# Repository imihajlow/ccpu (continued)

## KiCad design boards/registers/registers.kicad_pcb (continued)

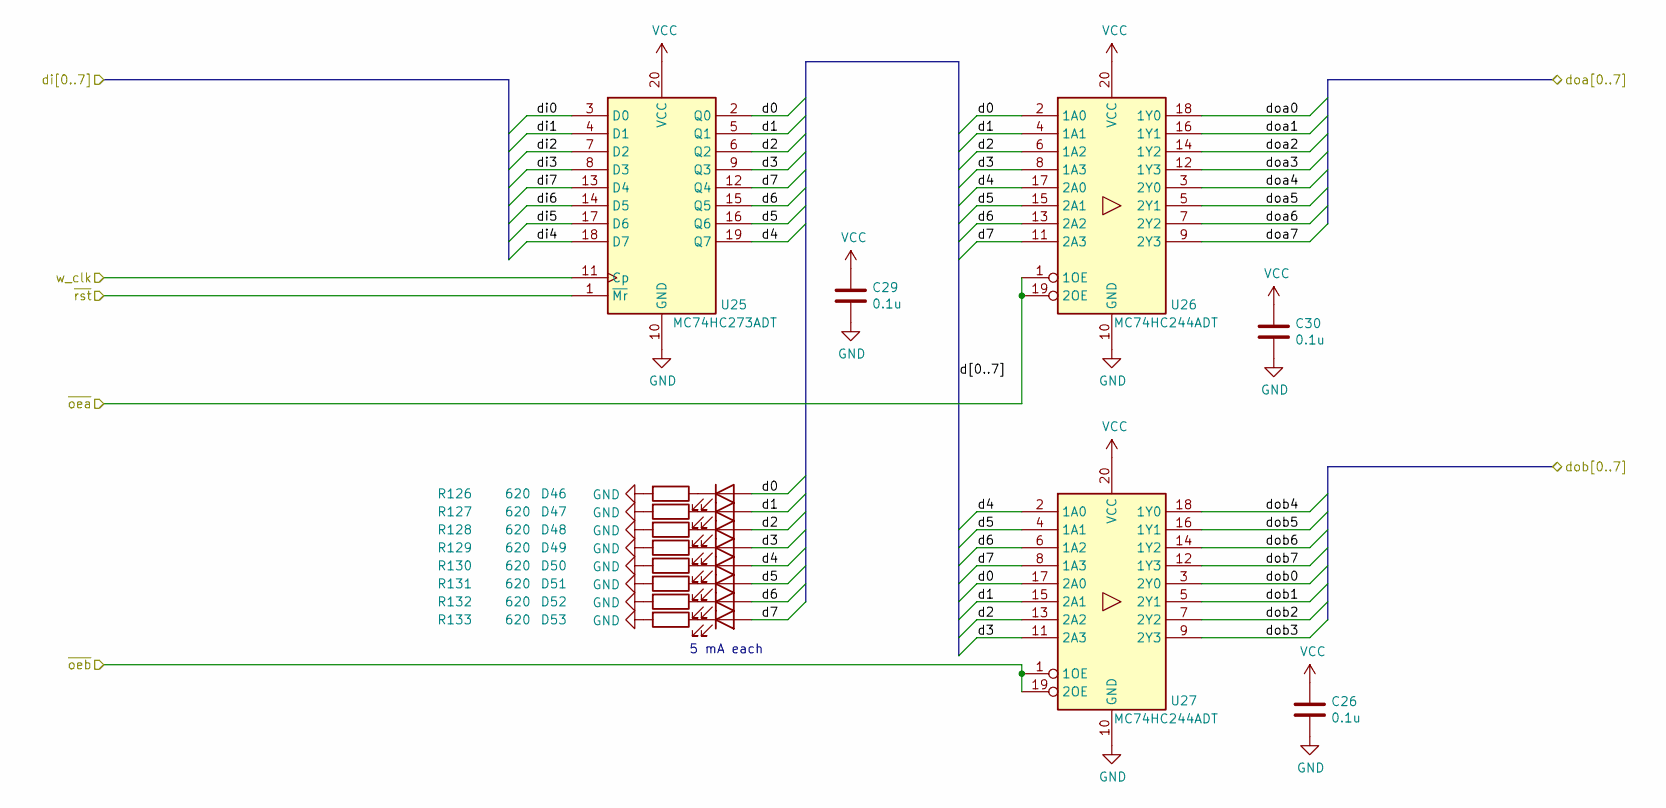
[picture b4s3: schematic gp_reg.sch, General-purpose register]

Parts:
C26, C29, C30: 0.1u; C_0805_2012Metric
D46, D47, D48, D49, D50, D51, D52, D53: KP-2012EC; LED_0805_2012Metric
R126, R127, R128, R129, R130, R131, R132, R133: 620; R_0805_2012Metric
U25: MC74HC273ADT; TSSOP-20_4.4x6.5mm_P0.65mm
U26, U27: MC74HC244ADT; TSSOP-20_4.4x6.5mm_P0.65mm

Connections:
/alu_b0: U27.3 (2Y0); also elsewhere on the board
/alu_b1: U27.5 (2Y1); also elsewhere on the board
/alu_b2: U27.7 (2Y2); also elsewhere on the board
/alu_b3: U27.9 (2Y3); also elsewhere on the board
/alu_b4: U27.18 (1Y0); also elsewhere on the board
/alu_b5: U27.16 (1Y1); also elsewhere on the board
/alu_b6: U27.14 (1Y2); also elsewhere on the board
/alu_b7: U27.12 (1Y3); also elsewhere on the board
/b_w_clk: U25.11 (Cp); also elsewhere on the board
/d0: U26.18 (1Y0); also elsewhere on the board
/d1: U26.16 (1Y1); also elsewhere on the board
/d2: U26.14 (1Y2); also elsewhere on the board
/d3: U26.12 (1Y3); also elsewhere on the board
/d4: U26.3 (2Y0); also elsewhere on the board
/d5: U26.5 (2Y1); also elsewhere on the board
/d6: U26.7 (2Y2); also elsewhere on the board
/d7: U26.9 (2Y3); also elsewhere on the board
/di0: U25.3 (D0); also elsewhere on the board
/di1: U25.4 (D1); also elsewhere on the board
/di2: U25.7 (D2); also elsewhere on the board
/di3: U25.8 (D3); also elsewhere on the board
/di4: U25.18 (D7); also elsewhere on the board
/di5: U25.17 (D6); also elsewhere on the board
/di6: U25.14 (D5); also elsewhere on the board
/di7: U25.13 (D4); also elsewhere on the board
/gp_reg_b/d0: D46.2 (A), U25.2 (Q0), U26.2 (1A0), U27.17 (2A0)
/gp_reg_b/d1: D47.2 (A), U25.5 (Q1), U26.4 (1A1), U27.15 (2A1)
/gp_reg_b/d2: D48.2 (A), U25.6 (Q2), U26.6 (1A2), U27.13 (2A2)
/gp_reg_b/d3: D49.2 (A), U25.9 (Q3), U26.8 (1A3), U27.11 (2A3)
/gp_reg_b/d4: D50.2 (A), U25.19 (Q7), U26.17 (2A0), U27.2 (1A0)
/gp_reg_b/d5: D51.2 (A), U25.16 (Q6), U26.15 (2A1), U27.4 (1A1)
/gp_reg_b/d6: D52.2 (A), U25.15 (Q5), U26.13 (2A2), U27.6 (1A2)
/gp_reg_b/d7: D53.2 (A), U25.12 (Q4), U26.11 (2A3), U27.8 (1A3)
/~oe_b_alu: U27.1 (1OE), U27.19 (2OE); also elsewhere on the board
/~oe_b_d: U26.1 (1OE), U26.19 (2OE); also elsewhere on the board
/~rst: U25.1 (~Mr); also elsewhere on the board
GND: C26.2, C29.2, C30.2, R126.2, R127.2, R128.2, R129.2, R130.2, R131.2, R132.2, R133.2, U25.10 (GND), U26.10 (GND), U27.10 (GND); also elsewhere on the board
unnamed: D46.1 (K), R126.1
unnamed: D47.1 (K), R127.1
unnamed: D48.1 (K), R128.1
unnamed: D49.1 (K), R129.1
unnamed: D50.1 (K), R130.1
unnamed: D51.1 (K), R131.1
unnamed: D52.1 (K), R132.1
unnamed: D53.1 (K), R133.1
VCC: C26.1, C29.1, C30.1, U25.20 (VCC), U26.20 (VCC), U27.20 (VCC); also elsewhere on the board

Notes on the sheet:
5 mA each

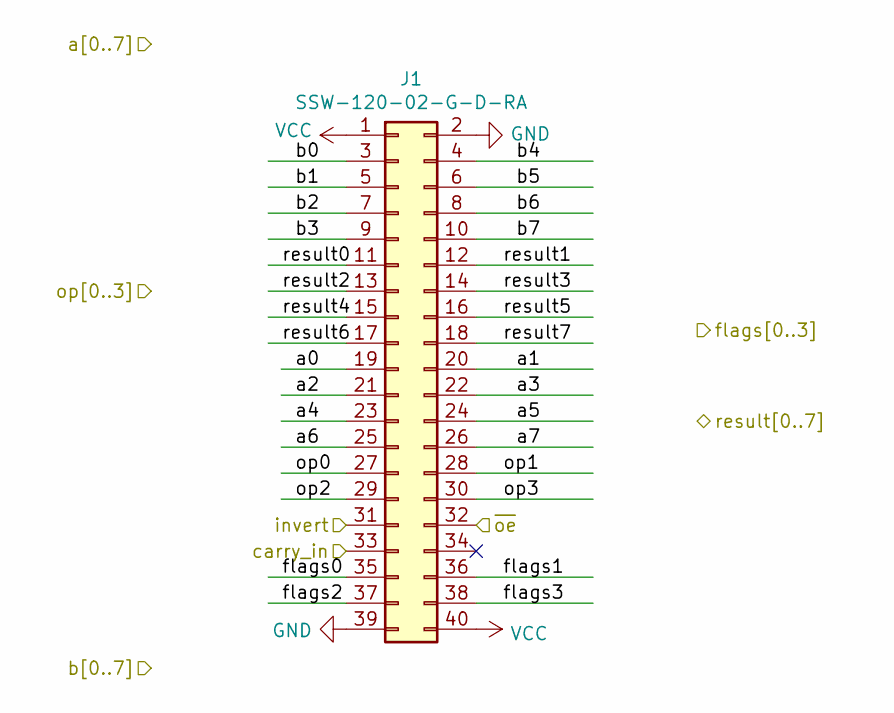
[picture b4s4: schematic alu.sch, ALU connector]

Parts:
J1: SSW-120-02-G-D-RA; PinSocket_2x20_P2.54mm_Horizontal

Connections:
/alu/a0: J1.19; also elsewhere on the board
/alu/a1: J1.20; also elsewhere on the board
/alu/a2: J1.21; also elsewhere on the board
/alu/a3: J1.22; also elsewhere on the board
/alu/a4: J1.23; also elsewhere on the board
/alu/a5: J1.24; also elsewhere on the board
/alu/a6: J1.25; also elsewhere on the board
/alu/a7: J1.26; also elsewhere on the board
/alu_b0: J1.3; also elsewhere on the board
/alu_b1: J1.5; also elsewhere on the board
/alu_b2: J1.7; also elsewhere on the board
/alu_b3: J1.9; also elsewhere on the board
/alu_b4: J1.4; also elsewhere on the board
/alu_b5: J1.6; also elsewhere on the board
/alu_b6: J1.8; also elsewhere on the board
/alu_b7: J1.10; also elsewhere on the board
/alu_invert: J1.31; also elsewhere on the board
/alu_op0: J1.27; also elsewhere on the board
/alu_op1: J1.28; also elsewhere on the board
/alu_op2: J1.29; also elsewhere on the board
/alu_op3: J1.30; also elsewhere on the board
/di0: J1.11; also elsewhere on the board
/di1: J1.12; also elsewhere on the board
/di2: J1.13; also elsewhere on the board
/di3: J1.14; also elsewhere on the board
/di4: J1.15; also elsewhere on the board
/di5: J1.16; also elsewhere on the board
/di6: J1.17; also elsewhere on the board
/di7: J1.18; also elsewhere on the board
/flags_in0: J1.35; also elsewhere on the board
/flags_in1: J1.36; also elsewhere on the board
/flags_in2: J1.37; also elsewhere on the board
/flags_in3: J1.38; also elsewhere on the board
/flags_out1: J1.33; also elsewhere on the board
/~oe_alu: J1.32; also elsewhere on the board
GND: J1.2, J1.39; also elsewhere on the board
VCC: J1.1, J1.40; also elsewhere on the board

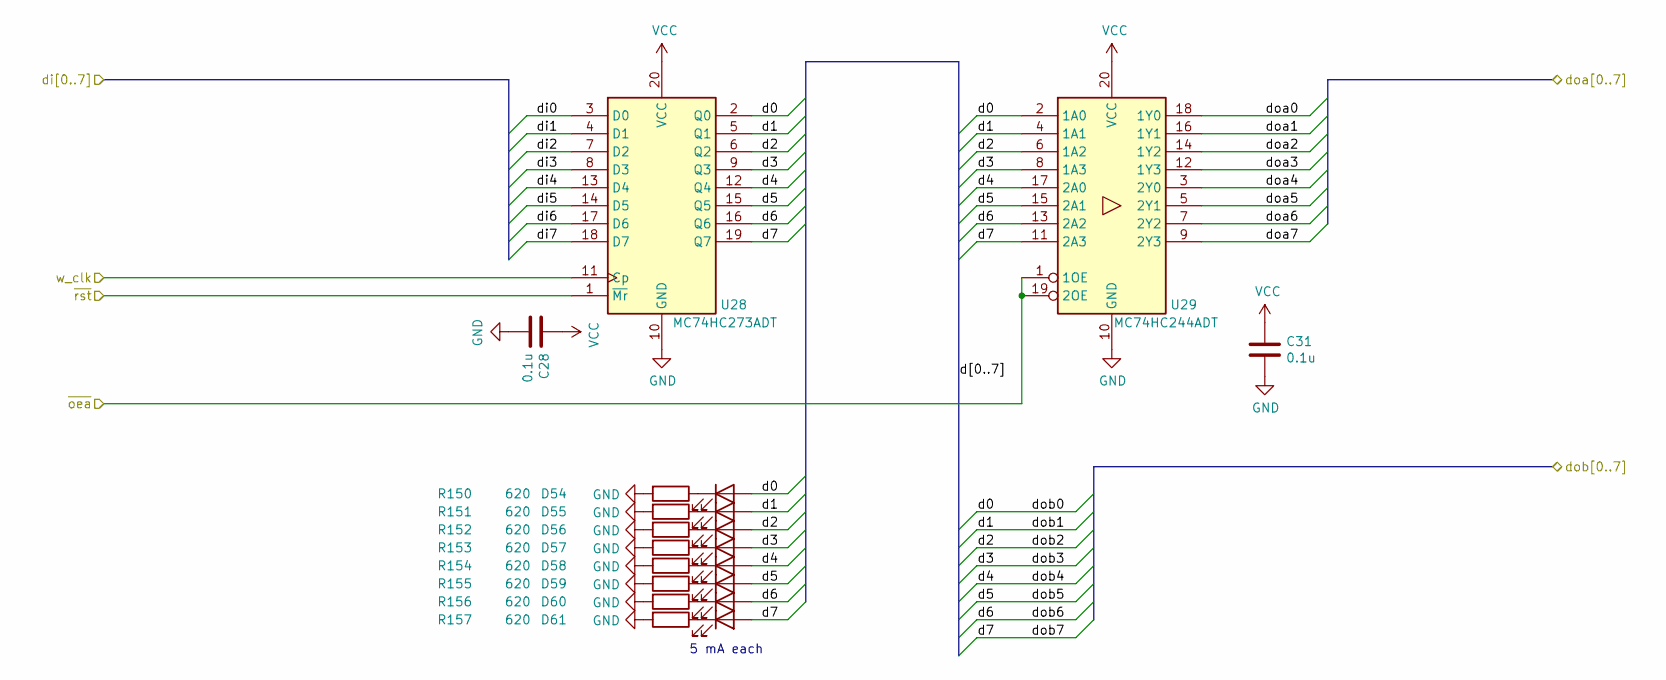
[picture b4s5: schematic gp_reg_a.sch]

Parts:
C28, C31: 0.1u; C_0805_2012Metric
D54, D55, D56, D57, D58, D59, D60, D61: KP-2012EC; LED_0805_2012Metric
R150, R151, R152, R153, R154, R155, R156, R157: 620; R_0805_2012Metric
U28: MC74HC273ADT; TSSOP-20_4.4x6.5mm_P0.65mm
U29: MC74HC244ADT; TSSOP-20_4.4x6.5mm_P0.65mm

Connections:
/a_w_clk: U28.11 (Cp); also elsewhere on the board
/alu/a0: D54.2 (A), U28.2 (Q0), U29.2 (1A0); also elsewhere on the board
/alu/a1: D55.2 (A), U28.5 (Q1), U29.4 (1A1); also elsewhere on the board
/alu/a2: D56.2 (A), U28.6 (Q2), U29.6 (1A2); also elsewhere on the board
/alu/a3: D57.2 (A), U28.9 (Q3), U29.8 (1A3); also elsewhere on the board
/alu/a4: D58.2 (A), U28.12 (Q4), U29.17 (2A0); also elsewhere on the board
/alu/a5: D59.2 (A), U28.15 (Q5), U29.15 (2A1); also elsewhere on the board
/alu/a6: D60.2 (A), U28.16 (Q6), U29.13 (2A2); also elsewhere on the board
/alu/a7: D61.2 (A), U28.19 (Q7), U29.11 (2A3); also elsewhere on the board
/d0: U29.18 (1Y0); also elsewhere on the board
/d1: U29.16 (1Y1); also elsewhere on the board
/d2: U29.14 (1Y2); also elsewhere on the board
/d3: U29.12 (1Y3); also elsewhere on the board
/d4: U29.3 (2Y0); also elsewhere on the board
/d5: U29.5 (2Y1); also elsewhere on the board
/d6: U29.7 (2Y2); also elsewhere on the board
/d7: U29.9 (2Y3); also elsewhere on the board
/di0: U28.3 (D0); also elsewhere on the board
/di1: U28.4 (D1); also elsewhere on the board
/di2: U28.7 (D2); also elsewhere on the board
/di3: U28.8 (D3); also elsewhere on the board
/di4: U28.13 (D4); also elsewhere on the board
/di5: U28.14 (D5); also elsewhere on the board
/di6: U28.17 (D6); also elsewhere on the board
/di7: U28.18 (D7); also elsewhere on the board
/~oe_a_d: U29.1 (1OE), U29.19 (2OE); also elsewhere on the board
/~rst: U28.1 (~Mr); also elsewhere on the board
GND: C28.2, C31.2, R150.2, R151.2, R152.2, R153.2, R154.2, R155.2, R156.2, R157.2, U28.10 (GND), U29.10 (GND); also elsewhere on the board
unnamed: D54.1 (K), R150.1
unnamed: D55.1 (K), R151.1
unnamed: D56.1 (K), R152.1
unnamed: D57.1 (K), R153.1
unnamed: D58.1 (K), R154.1
unnamed: D59.1 (K), R155.1
unnamed: D60.1 (K), R156.1
unnamed: D61.1 (K), R157.1
VCC: C28.1, C31.1, U28.20 (VCC), U29.20 (VCC); also elsewhere on the board

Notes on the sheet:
5 mA each

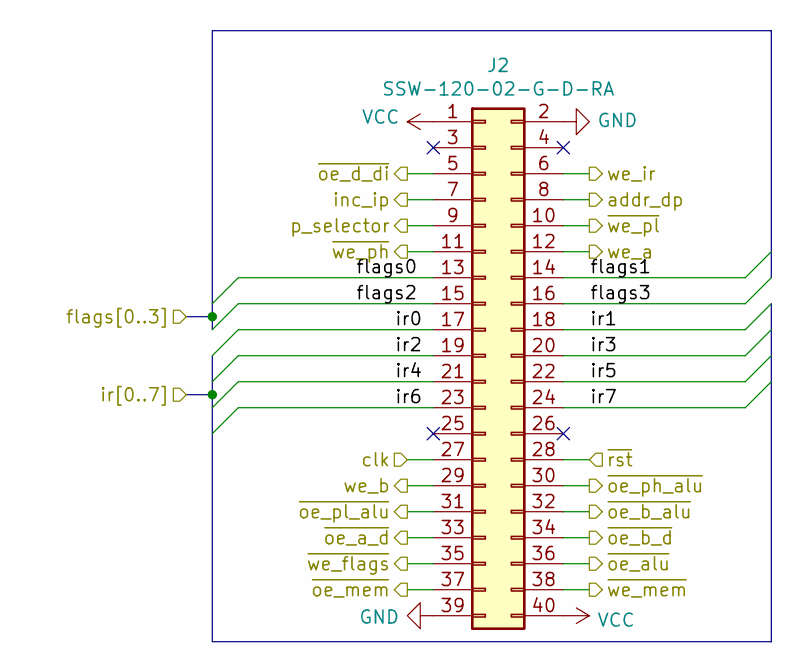
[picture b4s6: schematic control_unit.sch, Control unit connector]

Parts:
J2: SSW-120-02-G-D-RA; PinSocket_2x20_P2.54mm_Horizontal

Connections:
/addr_dp: J2.8; also elsewhere on the board
/alu_invert: J2.19; also elsewhere on the board
/alu_op0: J2.20; also elsewhere on the board
/alu_op1: J2.21; also elsewhere on the board
/alu_op2: J2.22; also elsewhere on the board
/alu_op3: J2.23; also elsewhere on the board
/clk: J2.27; also elsewhere on the board
/flags_out0: J2.13; also elsewhere on the board
/flags_out1: J2.14; also elsewhere on the board
/flags_out2: J2.15; also elsewhere on the board
/flags_out3: J2.16; also elsewhere on the board
/inc_ip: J2.7; also elsewhere on the board
/ir_out0: J2.17; also elsewhere on the board
/ir_out1: J2.18; also elsewhere on the board
/ir_out7: J2.24; also elsewhere on the board
/p_selector: J2.9; also elsewhere on the board
/we_a: J2.12; also elsewhere on the board
/we_b: J2.29; also elsewhere on the board
/we_ir: J2.6; also elsewhere on the board
/~oe: J2.37; also elsewhere on the board
/~oe_a_d: J2.33; also elsewhere on the board
/~oe_alu: J2.36; also elsewhere on the board
/~oe_b_alu: J2.32; also elsewhere on the board
/~oe_b_d: J2.34; also elsewhere on the board
/~oe_d_di: J2.5; also elsewhere on the board
/~oe_ph_alu: J2.30; also elsewhere on the board
/~oe_pl_alu: J2.31; also elsewhere on the board
/~rst: J2.28; also elsewhere on the board
/~we: J2.38; also elsewhere on the board
/~we_flags: J2.35; also elsewhere on the board
/~we_ph: J2.11; also elsewhere on the board
/~we_pl: J2.10; also elsewhere on the board
GND: J2.2, J2.39; also elsewhere on the board
VCC: J2.1, J2.40; also elsewhere on the board

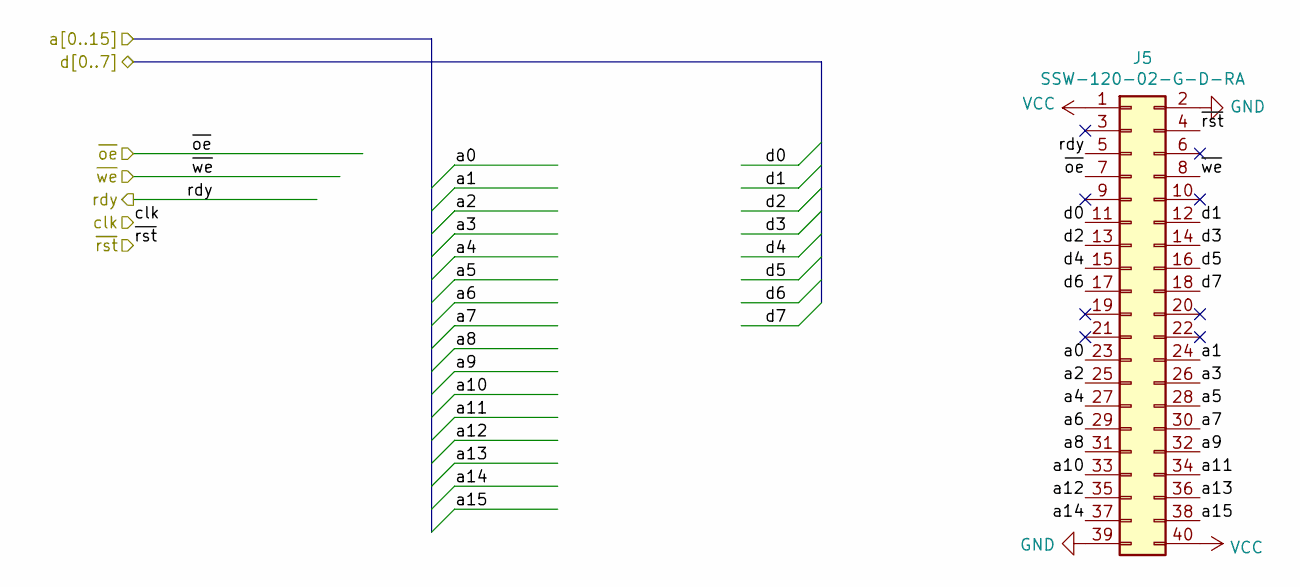
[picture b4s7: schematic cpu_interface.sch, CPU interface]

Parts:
J5: SSW-120-02-G-D-RA; PinSocket_2x20_P2.54mm_Horizontal

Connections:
/cpu_interface/a0: J5.23; also elsewhere on the board
/cpu_interface/a1: J5.24; also elsewhere on the board
/cpu_interface/a2: J5.25; also elsewhere on the board
/cpu_interface/a3: J5.26; also elsewhere on the board
/cpu_interface/a4: J5.27; also elsewhere on the board
/cpu_interface/a5: J5.28; also elsewhere on the board
/cpu_interface/a6: J5.29; also elsewhere on the board
/cpu_interface/a7: J5.30; also elsewhere on the board
/cpu_interface/a8: J5.31; also elsewhere on the board
/cpu_interface/a9: J5.32; also elsewhere on the board
/cpu_interface/a10: J5.33; also elsewhere on the board
/cpu_interface/a11: J5.34; also elsewhere on the board
/cpu_interface/a12: J5.35; also elsewhere on the board
/cpu_interface/a13: J5.36; also elsewhere on the board
/cpu_interface/a14: J5.37; also elsewhere on the board
/cpu_interface/a15: J5.38; also elsewhere on the board
/d0: J5.11; also elsewhere on the board
/d1: J5.12; also elsewhere on the board
/d2: J5.13; also elsewhere on the board
/d3: J5.14; also elsewhere on the board
/d4: J5.15; also elsewhere on the board
/d5: J5.16; also elsewhere on the board
/d6: J5.17; also elsewhere on the board
/d7: J5.18; also elsewhere on the board
/mem_rdy: J5.5; also elsewhere on the board
/~ext_rst: J5.4; also elsewhere on the board
/~oe: J5.7; also elsewhere on the board
/~we: J5.8; also elsewhere on the board
GND: J5.2, J5.39; also elsewhere on the board
VCC: J5.1, J5.40; also elsewhere on the board

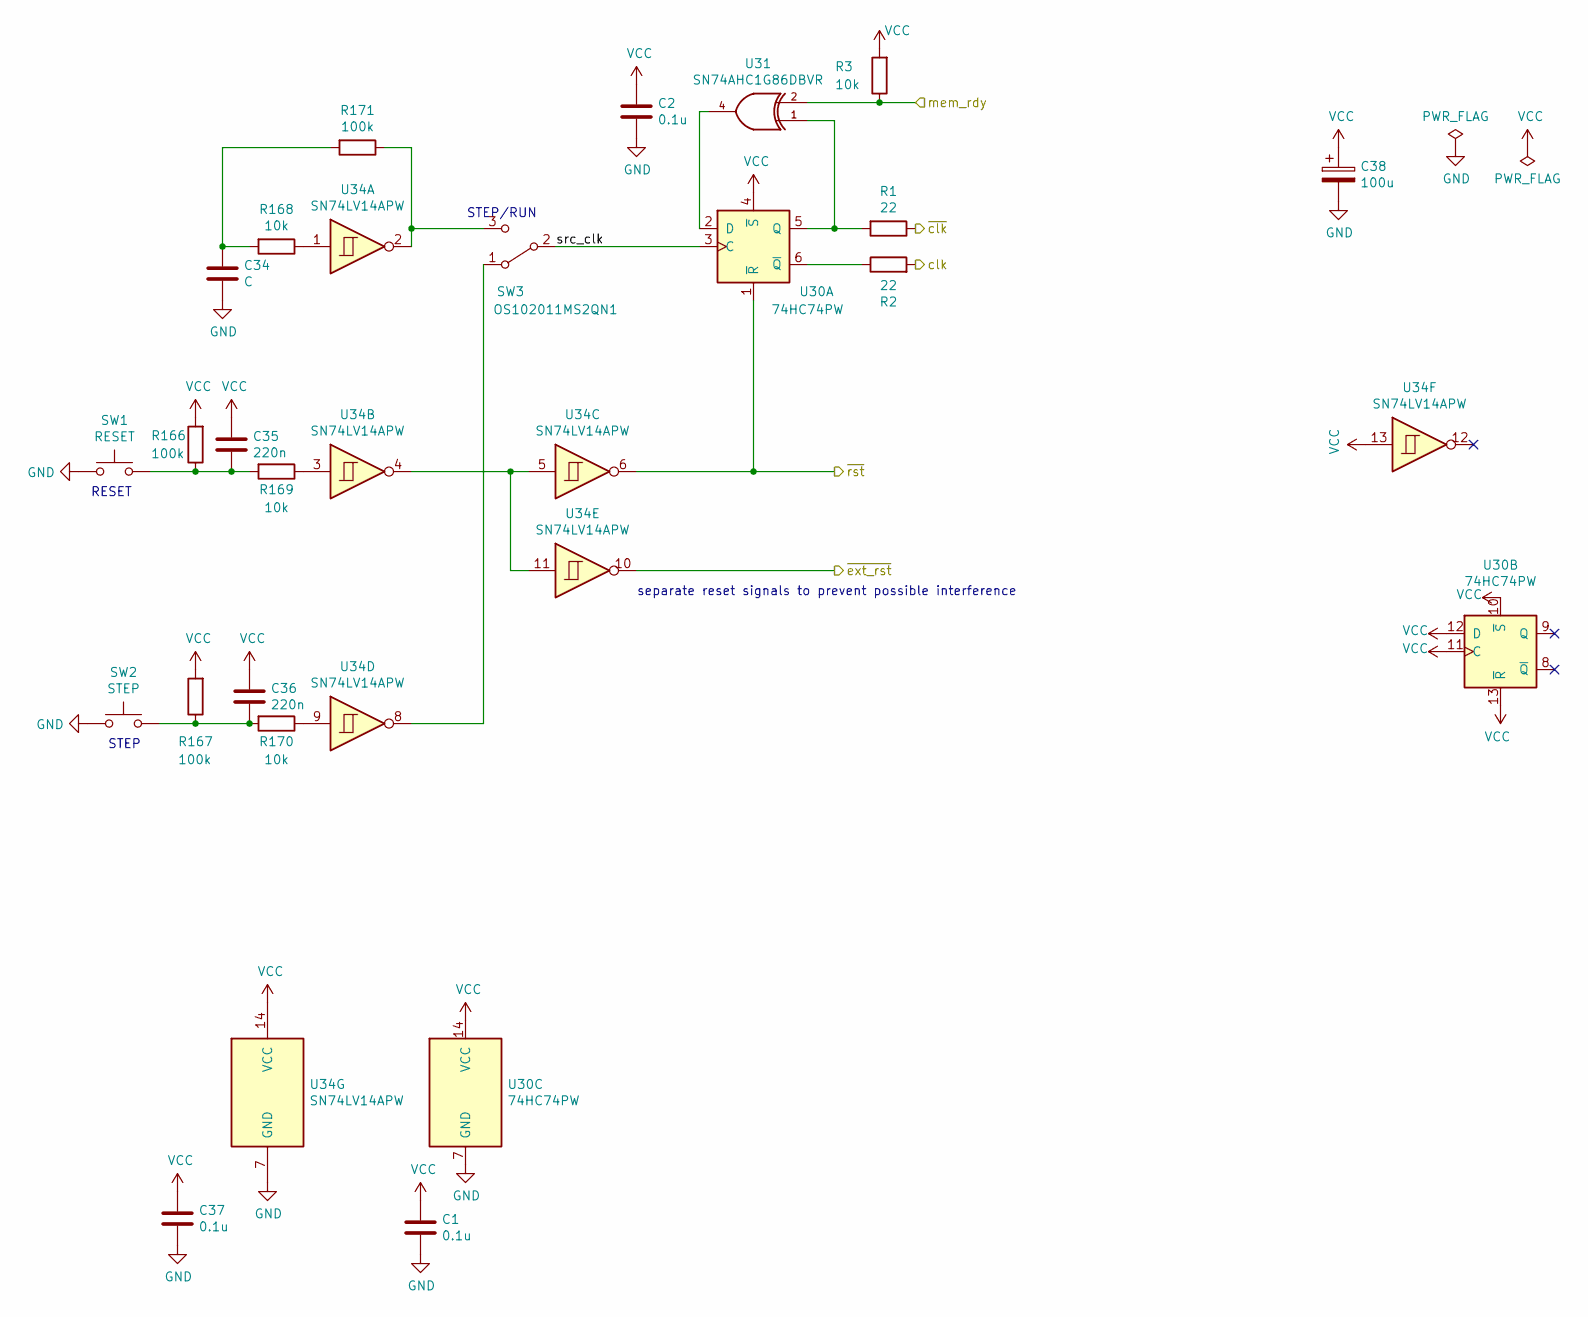
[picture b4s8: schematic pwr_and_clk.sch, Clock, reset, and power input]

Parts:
C1, C2, C37: 0.1u; C_0805_2012Metric
C34: C; C_0805_2012Metric
C35, C36: 220n; C_0805_2012Metric
C38: 100u; CP_EIA-3528-21_Kemet-B_Pad1.50x2.35mm_HandSolder
R1, R2: 22; R_0805_2012Metric
R3, R168, R169, R170: 10k; R_0805_2012Metric
R166, R167, R171: 100k; R_0805_2012Metric
SW1: RESET; SW_PUSH_6mm
SW2: STEP; SW_PUSH_6mm
SW3: OS102011MS2QN1; SW_Slide_1P2T_CK_OS102011MS2Q
U30: 74HC74PW; TSSOP-14_4.4x5mm_P0.65mm
U31: SN74AHC1G86DBVR; SOT-23-5
U34: SN74LV14APW; TSSOP-14_4.4x5mm_P0.65mm

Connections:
/clk: R2.2; also elsewhere on the board
/mem_rdy: R3.1, U31.2; also elsewhere on the board
/pwr_and_clk/src_clk: SW3.2 (B), U30.3 (C)
/~clk: R1.1; also elsewhere on the board
/~ext_rst: U34.10; also elsewhere on the board
/~rst: U30.1 (~R), U34.6; also elsewhere on the board
GND: C1.2, C2.2, C34.2, C37.2, C38.2, SW1.1, SW2.1, U30.7 (GND), U31.3 (GND), U34.7 (GND); also elsewhere on the board
unnamed: C34.1, R168.2, R171.2
unnamed: C35.2, R166.1, R169.2, SW1.2
unnamed: C36.2, R167.1, R170.2, SW2.2
unnamed: R1.2, U30.5 (Q), U31.1
unnamed: R2.1, U30.6 (~Q)
unnamed: R168.1, U34.1
unnamed: R169.1, U34.3
unnamed: R170.1, U34.9
unnamed: R171.1, SW3.3 (C), U34.2
unnamed: SW3.1 (A), U34.8
unnamed: U30.2 (D), U31.4
unnamed: U34.4, U34.5, U34.11
VCC: C1.1, C2.1, C35.1, C36.1, C37.1, C38.1, R3.2, R166.2, R167.2, U30.4 (~S), U30.10 (~S), U30.11 (C), U30.12 (D), U30.13 (~R), U30.14 (VCC), U31.5 (VCC), U34.13, U34.14 (VCC); also elsewhere on the board

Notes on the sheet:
STEP/RUN
RESET
STEP
separate reset signals to prevent possible interference

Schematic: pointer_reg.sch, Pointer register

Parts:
C10, C11, C13, C14, C15, C16, C17, C20: 0.1u; C_0805_2012Metric
D14, D15, D16, D17, D18, D19, D20, D21, D22, D23, D24, D25, D26, D27, D28, D29: KP-2012EC; LED_0805_2012Metric
R30, R31, R32, R33, R34, R35, R36, R37, R70, R71, R72, R73, R74, R75, R76, R77: 620; R_0805_2012Metric
U9, U10, U13, U14: 74HC161PW; TSSOP-16_4.4x5mm_P0.65mm
U11, U12, U15, U16: MC74HC244ADT; TSSOP-20_4.4x6.5mm_P0.65mm

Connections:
/alu_b0: U12.18 (1Y0), U15.18 (1Y0); also elsewhere on the board
/alu_b1: U12.16 (1Y1), U15.16 (1Y1); also elsewhere on the board
/alu_b2: U12.14 (1Y2), U15.14 (1Y2); also elsewhere on the board
/alu_b3: U12.12 (1Y3), U15.12 (1Y3); also elsewhere on the board
/alu_b4: U12.3 (2Y0), U15.3 (2Y0); also elsewhere on the board
/alu_b5: U12.5 (2Y1), U15.5 (2Y1); also elsewhere on the board
/alu_b6: U12.7 (2Y2), U15.7 (2Y2); also elsewhere on the board
/alu_b7: U12.9 (2Y3), U15.9 (2Y3); also elsewhere on the board
/cpu_interface/a0: U11.18 (1Y0); also elsewhere on the board
/cpu_interface/a1: U11.3 (2Y0); also elsewhere on the board
/cpu_interface/a2: U11.16 (1Y1); also elsewhere on the board
/cpu_interface/a3: U11.5 (2Y1); also elsewhere on the board
/cpu_interface/a4: U11.14 (1Y2); also elsewhere on the board
/cpu_interface/a5: U11.7 (2Y2); also elsewhere on the board
/cpu_interface/a6: U11.12 (1Y3); also elsewhere on the board
/cpu_interface/a7: U11.9 (2Y3); also elsewhere on the board
/cpu_interface/a8: U16.18 (1Y0); also elsewhere on the board
/cpu_interface/a9: U16.3 (2Y0); also elsewhere on the board
/cpu_interface/a10: U16.16 (1Y1); also elsewhere on the board
/cpu_interface/a11: U16.5 (2Y1); also elsewhere on the board
/cpu_interface/a12: U16.14 (1Y2); also elsewhere on the board
/cpu_interface/a13: U16.7 (2Y2); also elsewhere on the board
/cpu_interface/a14: U16.12 (1Y3); also elsewhere on the board
/cpu_interface/a15: U16.9 (2Y3); also elsewhere on the board
/di0: U9.3 (D0), U13.3 (D0); also elsewhere on the board
/di1: U9.4 (D1), U13.4 (D1); also elsewhere on the board
/di2: U9.5 (D2), U13.5 (D2); also elsewhere on the board
/di3: U9.6 (D3), U13.6 (D3); also elsewhere on the board
/di4: U10.3 (D0), U14.3 (D0); also elsewhere on the board
/di5: U10.4 (D1), U14.4 (D1); also elsewhere on the board
/di6: U10.5 (D2), U14.5 (D2); also elsewhere on the board
/di7: U10.6 (D3), U14.6 (D3); also elsewhere on the board
/pointer_pair/reg_a/cnt: U9.7 (CEP), U9.10 (CET), U10.7 (CEP), U13.7 (CEP), U14.7 (CEP); also elsewhere on the board
/pointer_pair/reg_a/hi0: D22.2 (A), U13.14 (Q0), U15.2 (1A0), U16.2 (1A0)
/pointer_pair/reg_a/hi1: D23.2 (A), U13.13 (Q1), U15.4 (1A1), U16.17 (2A0)
/pointer_pair/reg_a/hi2: D24.2 (A), U13.12 (Q2), U15.6 (1A2), U16.4 (1A1)
/pointer_pair/reg_a/hi3: D25.2 (A), U13.11 (Q3), U15.8 (1A3), U16.15 (2A1)
/pointer_pair/reg_a/hi4: D26.2 (A), U14.14 (Q0), U15.17 (2A0), U16.6 (1A2)
/pointer_pair/reg_a/hi5: D27.2 (A), U14.13 (Q1), U15.15 (2A1), U16.13 (2A2)
/pointer_pair/reg_a/hi6: D28.2 (A), U14.12 (Q2), U15.13 (2A2), U16.8 (1A3)
/pointer_pair/reg_a/hi7: D29.2 (A), U14.11 (Q3), U15.11 (2A3), U16.11 (2A3)
/pointer_pair/reg_a/lo0: D14.2 (A), U9.14 (Q0), U11.2 (1A0), U12.2 (1A0)
/pointer_pair/reg_a/lo1: D15.2 (A), U9.13 (Q1), U11.17 (2A0), U12.4 (1A1)
/pointer_pair/reg_a/lo2: D16.2 (A), U9.12 (Q2), U11.4 (1A1), U12.6 (1A2)
/pointer_pair/reg_a/lo3: D17.2 (A), U9.11 (Q3), U11.15 (2A1), U12.8 (1A3)
/pointer_pair/reg_a/lo4: D18.2 (A), U10.14 (Q0), U11.6 (1A2), U12.17 (2A0)
/pointer_pair/reg_a/lo5: D19.2 (A), U10.13 (Q1), U11.13 (2A2), U12.15 (2A1)
/pointer_pair/reg_a/lo6: D20.2 (A), U10.12 (Q2), U11.8 (1A3), U12.13 (2A2)
/pointer_pair/reg_a/lo7: D21.2 (A), U10.11 (Q3), U11.11 (2A3), U12.11 (2A3)
/pointer_pair/reg_a/~oe_dh: U15.1 (1OE), U15.19 (2OE); also elsewhere on the board
/pointer_pair/reg_a/~oe_dl: U12.1 (1OE), U12.19 (2OE); also elsewhere on the board
/pointer_pair/reg_a/~we_h: U13.9 (~PE), U14.9 (~PE); also elsewhere on the board
/pointer_pair/reg_a/~we_l: U9.9 (~PE), U10.9 (~PE); also elsewhere on the board
/pointer_pair/~a_oe_addr: U11.1 (1OE), U11.19 (2OE), U16.1 (1OE), U16.19 (2OE); also elsewhere on the board
/~clk: U9.2 (CP), U10.2 (CP), U13.2 (CP), U14.2 (CP); also elsewhere on the board
/~rst: U9.1 (~MR), U10.1 (~MR), U13.1 (~MR), U14.1 (~MR); also elsewhere on the board
GND: C10.2, C11.2, C13.2, C14.2, C15.2, C16.2, C17.2, C20.2, R30.1, R31.1, R32.1, R33.1, R34.1, R35.1, R36.1, R37.1, R70.1, R71.1, R72.1, R73.1, R74.1, R75.1, R76.1, R77.1, U9.8 (GND), U10.8 (GND), U11.10 (GND), U12.10 (GND), U13.8 (GND), U14.8 (GND), U15.10 (GND), U16.10 (GND); also elsewhere on the board
unnamed: D14.1 (K), R30.2
unnamed: D15.1 (K), R31.2
unnamed: D16.1 (K), R32.2
unnamed: D17.1 (K), R33.2
unnamed: D18.1 (K), R34.2
unnamed: D19.1 (K), R35.2
unnamed: D20.1 (K), R36.2
unnamed: D21.1 (K), R37.2
unnamed: D22.1 (K), R70.2
unnamed: D23.1 (K), R71.2
unnamed: D24.1 (K), R72.2
unnamed: D25.1 (K), R73.2
unnamed: D26.1 (K), R74.2
unnamed: D27.1 (K), R75.2
unnamed: D28.1 (K), R76.2
unnamed: D29.1 (K), R77.2
unnamed: U9.15 (TC), U10.10 (CET)
unnamed: U10.15 (TC), U13.10 (CET)
unnamed: U13.15 (TC), U14.10 (CET)
VCC: C10.1, C11.1, C13.1, C14.1, C15.1, C16.1, C17.1, C20.1, U9.16 (VCC), U10.16 (VCC), U11.20 (VCC), U12.20 (VCC), U13.16 (VCC), U14.16 (VCC), U15.20 (VCC), U16.20 (VCC); also elsewhere on the board

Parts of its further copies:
C18, C19, C21, C22, C23, C24, C25, C27: 0.1u; C_0805_2012Metric
D30, D31, D32, D33, D34, D35, D36, D37, D38, D39, D40, D41, D42, D43, D44, D45: KP-2012EC; LED_0805_2012Metric
R78, R79, R80, R81, R82, R83, R84, R85, R118, R119, R120, R121, R122, R123, R124, R125: 620; R_0805_2012Metric
U17, U18, U21, U22: 74HC161PW; TSSOP-16_4.4x5mm_P0.65mm
U19, U20, U23, U24: MC74HC244ADT; TSSOP-20_4.4x6.5mm_P0.65mm

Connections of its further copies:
/alu_b0: U20.18 (1Y0), U23.18 (1Y0); also elsewhere on the board
/alu_b1: U20.16 (1Y1), U23.16 (1Y1); also elsewhere on the board
/alu_b2: U20.14 (1Y2), U23.14 (1Y2); also elsewhere on the board
/alu_b3: U20.12 (1Y3), U23.12 (1Y3); also elsewhere on the board
/alu_b4: U20.3 (2Y0), U23.3 (2Y0); also elsewhere on the board
/alu_b5: U20.5 (2Y1), U23.5 (2Y1); also elsewhere on the board
/alu_b6: U20.7 (2Y2), U23.7 (2Y2); also elsewhere on the board
/alu_b7: U20.9 (2Y3), U23.9 (2Y3); also elsewhere on the board
/cpu_interface/a0: U19.18 (1Y0); also elsewhere on the board
/cpu_interface/a1: U19.3 (2Y0); also elsewhere on the board
/cpu_interface/a2: U19.16 (1Y1); also elsewhere on the board
/cpu_interface/a3: U19.5 (2Y1); also elsewhere on the board
/cpu_interface/a4: U19.14 (1Y2); also elsewhere on the board
/cpu_interface/a5: U19.7 (2Y2); also elsewhere on the board
/cpu_interface/a6: U19.12 (1Y3); also elsewhere on the board
/cpu_interface/a7: U19.9 (2Y3); also elsewhere on the board
/cpu_interface/a8: U24.18 (1Y0); also elsewhere on the board
/cpu_interface/a9: U24.3 (2Y0); also elsewhere on the board
/cpu_interface/a10: U24.16 (1Y1); also elsewhere on the board
/cpu_interface/a11: U24.5 (2Y1); also elsewhere on the board
/cpu_interface/a12: U24.14 (1Y2); also elsewhere on the board
/cpu_interface/a13: U24.7 (2Y2); also elsewhere on the board
/cpu_interface/a14: U24.12 (1Y3); also elsewhere on the board
/cpu_interface/a15: U24.9 (2Y3); also elsewhere on the board
/di0: U17.3 (D0), U21.3 (D0); also elsewhere on the board
/di1: U17.4 (D1), U21.4 (D1); also elsewhere on the board
/di2: U17.5 (D2), U21.5 (D2); also elsewhere on the board
/di3: U17.6 (D3), U21.6 (D3); also elsewhere on the board
/di4: U18.3 (D0), U22.3 (D0); also elsewhere on the board
/di5: U18.4 (D1), U22.4 (D1); also elsewhere on the board
/di6: U18.5 (D2), U22.5 (D2); also elsewhere on the board
/di7: U18.6 (D3), U22.6 (D3); also elsewhere on the board
/pointer_pair/reg_b/cnt: U17.7 (CEP), U17.10 (CET), U18.7 (CEP), U21.7 (CEP), U22.7 (CEP); also elsewhere on the board
/pointer_pair/reg_b/hi0: D38.2 (A), U21.14 (Q0), U23.2 (1A0), U24.2 (1A0)
/pointer_pair/reg_b/hi1: D39.2 (A), U21.13 (Q1), U23.4 (1A1), U24.17 (2A0)
/pointer_pair/reg_b/hi2: D40.2 (A), U21.12 (Q2), U23.6 (1A2), U24.4 (1A1)
/pointer_pair/reg_b/hi3: D41.2 (A), U21.11 (Q3), U23.8 (1A3), U24.15 (2A1)
/pointer_pair/reg_b/hi4: D42.2 (A), U22.14 (Q0), U23.17 (2A0), U24.6 (1A2)
/pointer_pair/reg_b/hi5: D43.2 (A), U22.13 (Q1), U23.15 (2A1), U24.13 (2A2)
/pointer_pair/reg_b/hi6: D44.2 (A), U22.12 (Q2), U23.13 (2A2), U24.8 (1A3)
/pointer_pair/reg_b/hi7: D45.2 (A), U22.11 (Q3), U23.11 (2A3), U24.11 (2A3)
/pointer_pair/reg_b/lo0: D30.2 (A), U17.14 (Q0), U19.2 (1A0), U20.2 (1A0)
/pointer_pair/reg_b/lo1: D31.2 (A), U17.13 (Q1), U19.17 (2A0), U20.4 (1A1)
/pointer_pair/reg_b/lo2: D32.2 (A), U17.12 (Q2), U19.4 (1A1), U20.6 (1A2)
/pointer_pair/reg_b/lo3: D33.2 (A), U17.11 (Q3), U19.15 (2A1), U20.8 (1A3)
/pointer_pair/reg_b/lo4: D34.2 (A), U18.14 (Q0), U19.6 (1A2), U20.17 (2A0)
/pointer_pair/reg_b/lo5: D35.2 (A), U18.13 (Q1), U19.13 (2A2), U20.15 (2A1)
/pointer_pair/reg_b/lo6: D36.2 (A), U18.12 (Q2), U19.8 (1A3), U20.13 (2A2)
/pointer_pair/reg_b/lo7: D37.2 (A), U18.11 (Q3), U19.11 (2A3), U20.11 (2A3)
/pointer_pair/reg_b/~oe_dh: U23.1 (1OE), U23.19 (2OE); also elsewhere on the board
/pointer_pair/reg_b/~oe_dl: U20.1 (1OE), U20.19 (2OE); also elsewhere on the board
/pointer_pair/reg_b/~we_h: U21.9 (~PE), U22.9 (~PE); also elsewhere on the board
/pointer_pair/reg_b/~we_l: U17.9 (~PE), U18.9 (~PE); also elsewhere on the board
/pointer_pair/~b_oe_addr: U19.1 (1OE), U19.19 (2OE), U24.1 (1OE), U24.19 (2OE); also elsewhere on the board
/~clk: U17.2 (CP), U18.2 (CP), U21.2 (CP), U22.2 (CP); also elsewhere on the board
/~rst: U17.1 (~MR), U18.1 (~MR), U21.1 (~MR), U22.1 (~MR); also elsewhere on the board
GND: C18.2, C19.2, C21.2, C22.2, C23.2, C24.2, C25.2, C27.2, R78.1, R79.1, R80.1, R81.1, R82.1, R83.1, R84.1, R85.1, R118.1, R119.1, R120.1, R121.1, R122.1, R123.1, R124.1, R125.1, U17.8 (GND), U18.8 (GND), U19.10 (GND), U20.10 (GND), U21.8 (GND), U22.8 (GND), U23.10 (GND), U24.10 (GND); also elsewhere on the board
unnamed: D30.1 (K), R78.2
unnamed: D31.1 (K), R79.2
unnamed: D32.1 (K), R80.2
unnamed: D33.1 (K), R81.2
unnamed: D34.1 (K), R82.2
unnamed: D35.1 (K), R83.2
unnamed: D36.1 (K), R84.2
unnamed: D37.1 (K), R85.2
unnamed: D38.1 (K), R118.2
unnamed: D39.1 (K), R119.2
unnamed: D40.1 (K), R120.2
unnamed: D41.1 (K), R121.2
unnamed: D42.1 (K), R122.2
unnamed: D43.1 (K), R123.2
unnamed: D44.1 (K), R124.2
unnamed: D45.1 (K), R125.2
unnamed: U17.15 (TC), U18.10 (CET)
unnamed: U18.15 (TC), U21.10 (CET)
unnamed: U21.15 (TC), U22.10 (CET)
VCC: C18.1, C19.1, C21.1, C22.1, C23.1, C24.1, C25.1, C27.1, U17.16 (VCC), U18.16 (VCC), U19.20 (VCC), U20.20 (VCC), U21.16 (VCC), U22.16 (VCC), U23.20 (VCC), U24.20 (VCC); also elsewhere on the board

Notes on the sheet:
The resistor values are such that each LED is driven by 10 mA (prevent 74ACT161 overload).
